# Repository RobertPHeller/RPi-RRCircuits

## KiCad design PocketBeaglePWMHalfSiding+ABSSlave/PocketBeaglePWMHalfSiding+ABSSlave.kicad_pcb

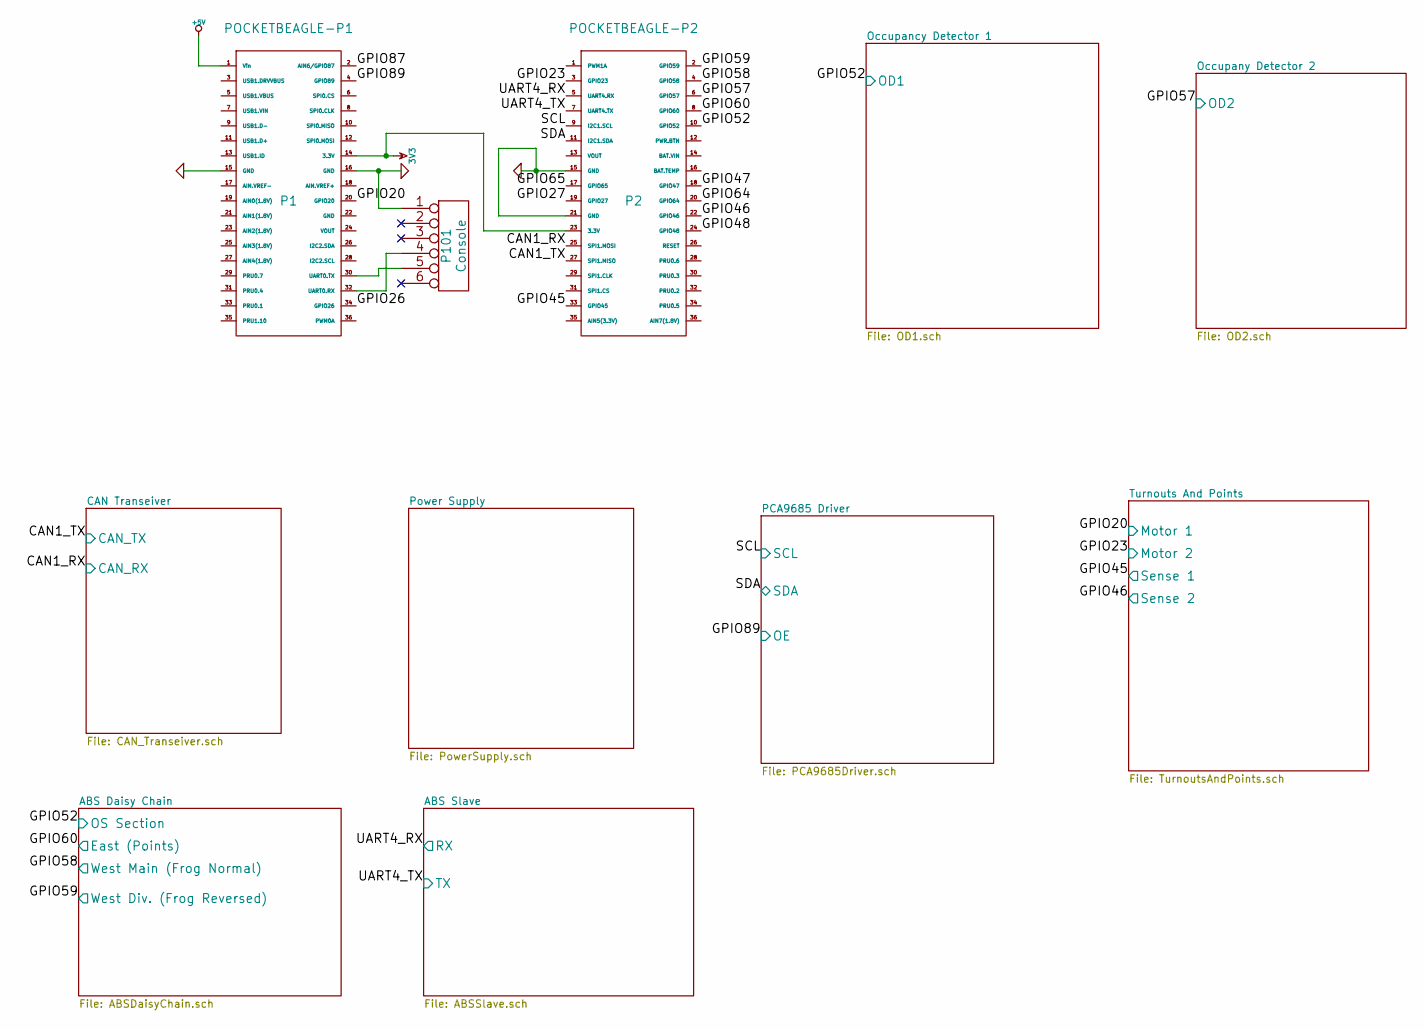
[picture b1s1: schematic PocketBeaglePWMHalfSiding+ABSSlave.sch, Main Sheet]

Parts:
P1: POCKETBEAGLE-P1
P2: POCKETBEAGLE-P2
P101: Console

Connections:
3V3: P1.14 (3.3V), P2.23 (3.3V); also elsewhere on the board
+5V: P1.1 (Vin); also elsewhere on the board
/ABS Daisy Chain/East (Points): P2.8 (GPIO60); also elsewhere on the board
/ABS Daisy Chain/West Div. (Frog Reversed): P2.2 (GPIO59); also elsewhere on the board
/ABS Daisy Chain/West Main (Frog Normal): P2.4 (GPIO58); also elsewhere on the board
/ABS Slave/RX: P2.5 (UART4.RX); also elsewhere on the board
/ABS Slave/TX: P2.7 (UART4.TX); also elsewhere on the board
/CAN Transeiver/CAN_RX: P2.25 (SPI1.MOSI); also elsewhere on the board
/CAN Transeiver/CAN_TX: P2.27 (SPI1.MISO); also elsewhere on the board
/Occupancy Detector 1/OD1: P2.10 (GPIO52); also elsewhere on the board
/Occupany Detector 2/OD2: P2.6 (GPIO57); also elsewhere on the board
/PCA9685 Driver/OE: P1.4 (GPIO89); also elsewhere on the board
/PCA9685 Driver/SCL: P2.9 (I2C1.SCL); also elsewhere on the board
/PCA9685 Driver/SDA: P2.11 (I2C1.SDA); also elsewhere on the board
/Turnouts And Points/Motor 1: P1.20 (GPIO20); also elsewhere on the board
/Turnouts And Points/Motor 2: P2.3 (GPIO23); also elsewhere on the board
/Turnouts And Points/Sense 1: P2.33 (GPIO45); also elsewhere on the board
/Turnouts And Points/Sense 2: P2.22 (GPIO46); also elsewhere on the board
GND: P1.15 (GND), P1.16 (GND), P2.15 (GND), P2.21 (GND), P101.1; also elsewhere on the board
unnamed: P1.32 (UART0.RX), P101.4
unnamed: P1.30 (UART0.TX), P101.5

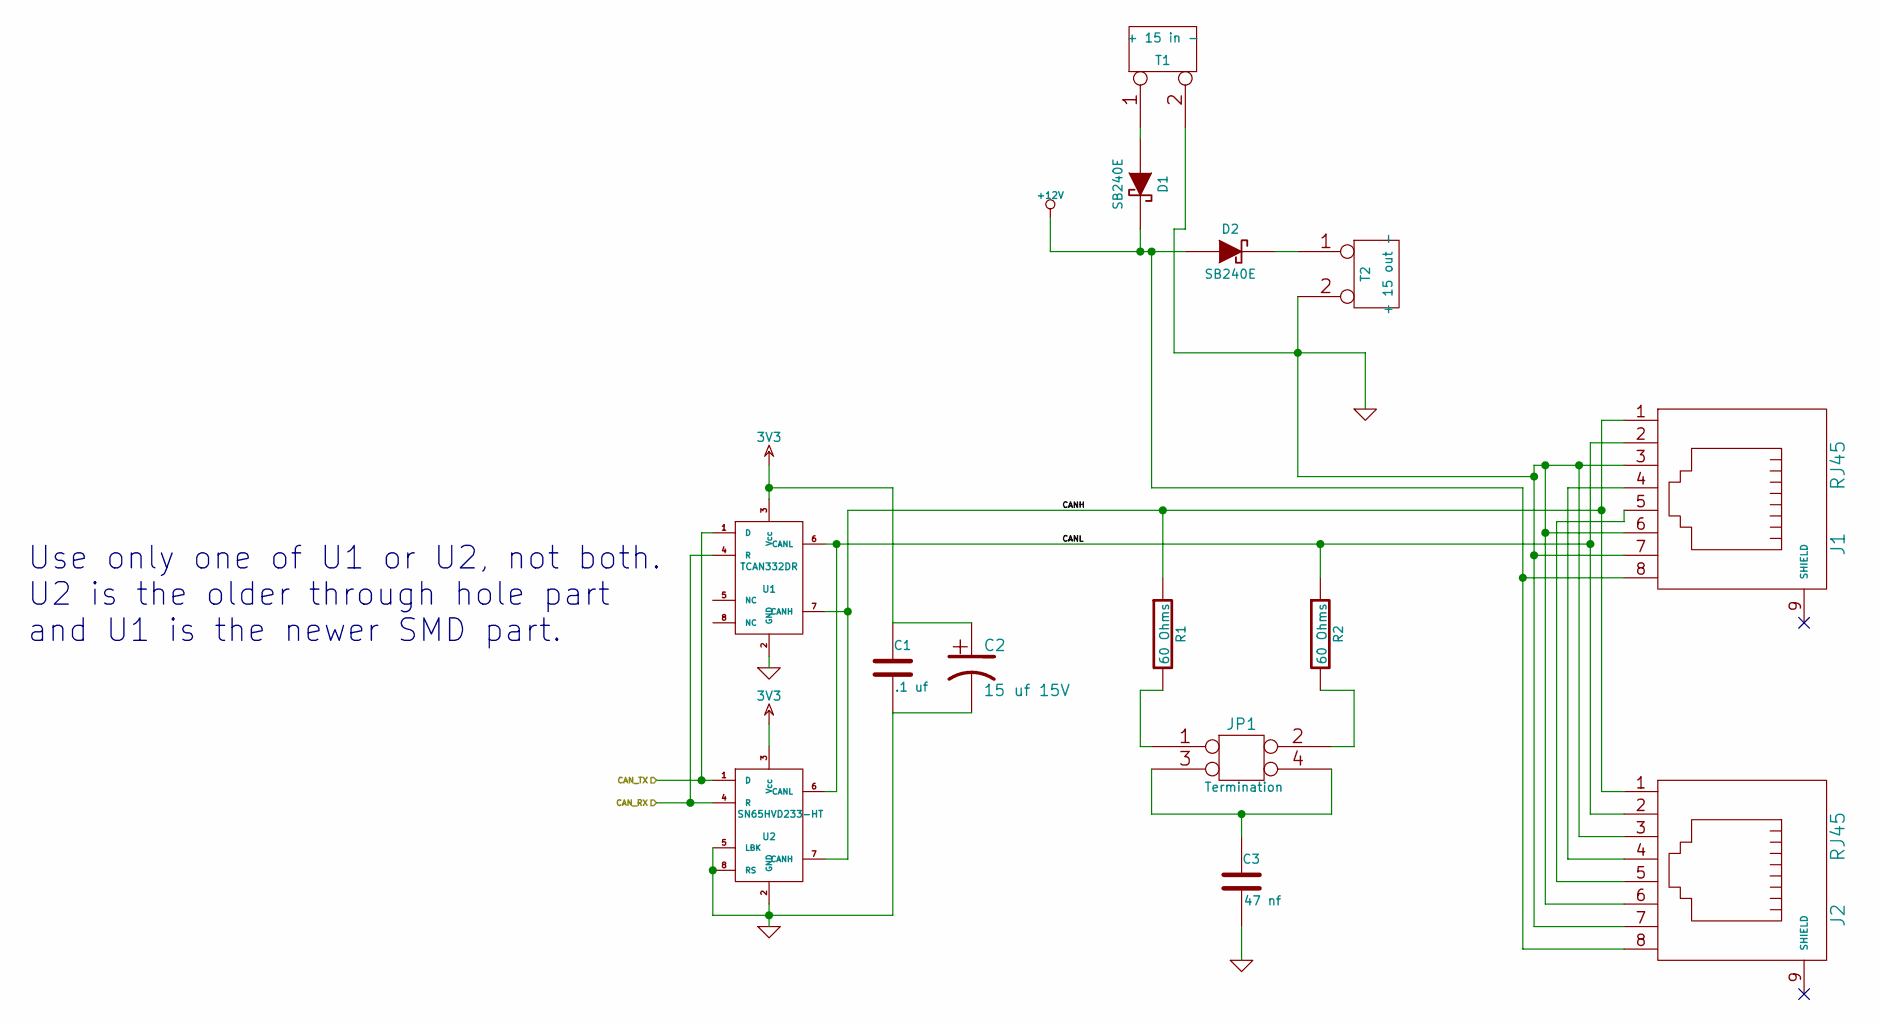
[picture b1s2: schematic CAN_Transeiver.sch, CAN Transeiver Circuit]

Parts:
C1: .1 uf
C2: 15 uf 15V
C3: 47 nf
D1, D2: SB240E
J1, J2: RJ45
JP1: Termination
R1, R2: 60 Ohms
T1: + 15 in -
T2: + 15 out -
U1: TCAN332DR
U2: SN65HVD233-HT

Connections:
3V3: C1.1, C2.1, U1.3 (Vcc), U2.3 (Vcc); also elsewhere on the board
+12V: D1.2 (K), D2.1 (A), J1.8, J2.8; also elsewhere on the board
/CAN Transeiver/CANH: J1.1, J2.1, R1.1, U1.7 (CANH), U2.7 (CANH)
/CAN Transeiver/CANL: J1.2, J2.2, R2.1, U1.6 (CANL), U2.6 (CANL)
/CAN Transeiver/CAN_RX: U1.4 (R), U2.4 (R); also elsewhere on the board
/CAN Transeiver/CAN_TX: U1.1 (D), U2.1 (D); also elsewhere on the board
GND: C1.2, C2.2, C3.2, J1.3, J1.6, J1.7, J2.3, J2.6, J2.7, T1.2 (PM), T2.2 (PM), U1.2 (GND), U2.2 (GND), U2.5 (LBK), U2.8 (RS); also elsewhere on the board
unnamed: J1.4, J2.4
unnamed: J1.5, J2.5
unnamed: D1.1 (A), T1.1
unnamed: D2.2 (K), T2.1
unnamed: JP1.1, R1.2
unnamed: JP1.2, R2.2
unnamed: C3.1, JP1.3, JP1.4

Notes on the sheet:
Use only one of U1 or U2, not both. U2 is the older through hole part and U1 is the newer SMD part.

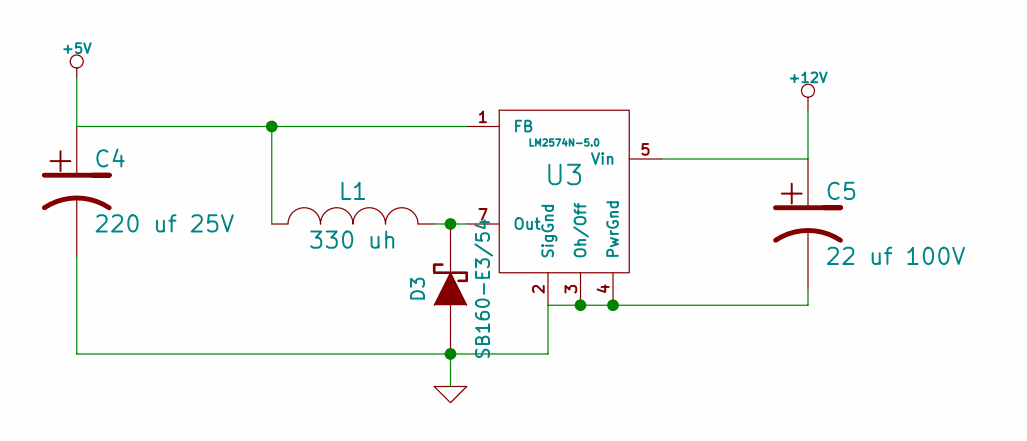
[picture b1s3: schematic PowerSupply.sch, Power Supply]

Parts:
C4: 220 uf 25V
C5: 22 uf 100V
D3: SB160-E3/54
L1: 330 uh
U3: LM2574N-5.0

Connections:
+5V: C4.1, L1.1, U3.1 (FB); also elsewhere on the board
+12V: C5.1, U3.5 (Vin); also elsewhere on the board
GND: C4.2, C5.2, D3.1 (A), U3.2 (SigGnd), U3.3 (Oh/Off), U3.4 (PwrGnd); also elsewhere on the board
unnamed: D3.2 (K), L1.2, U3.7 (Out)

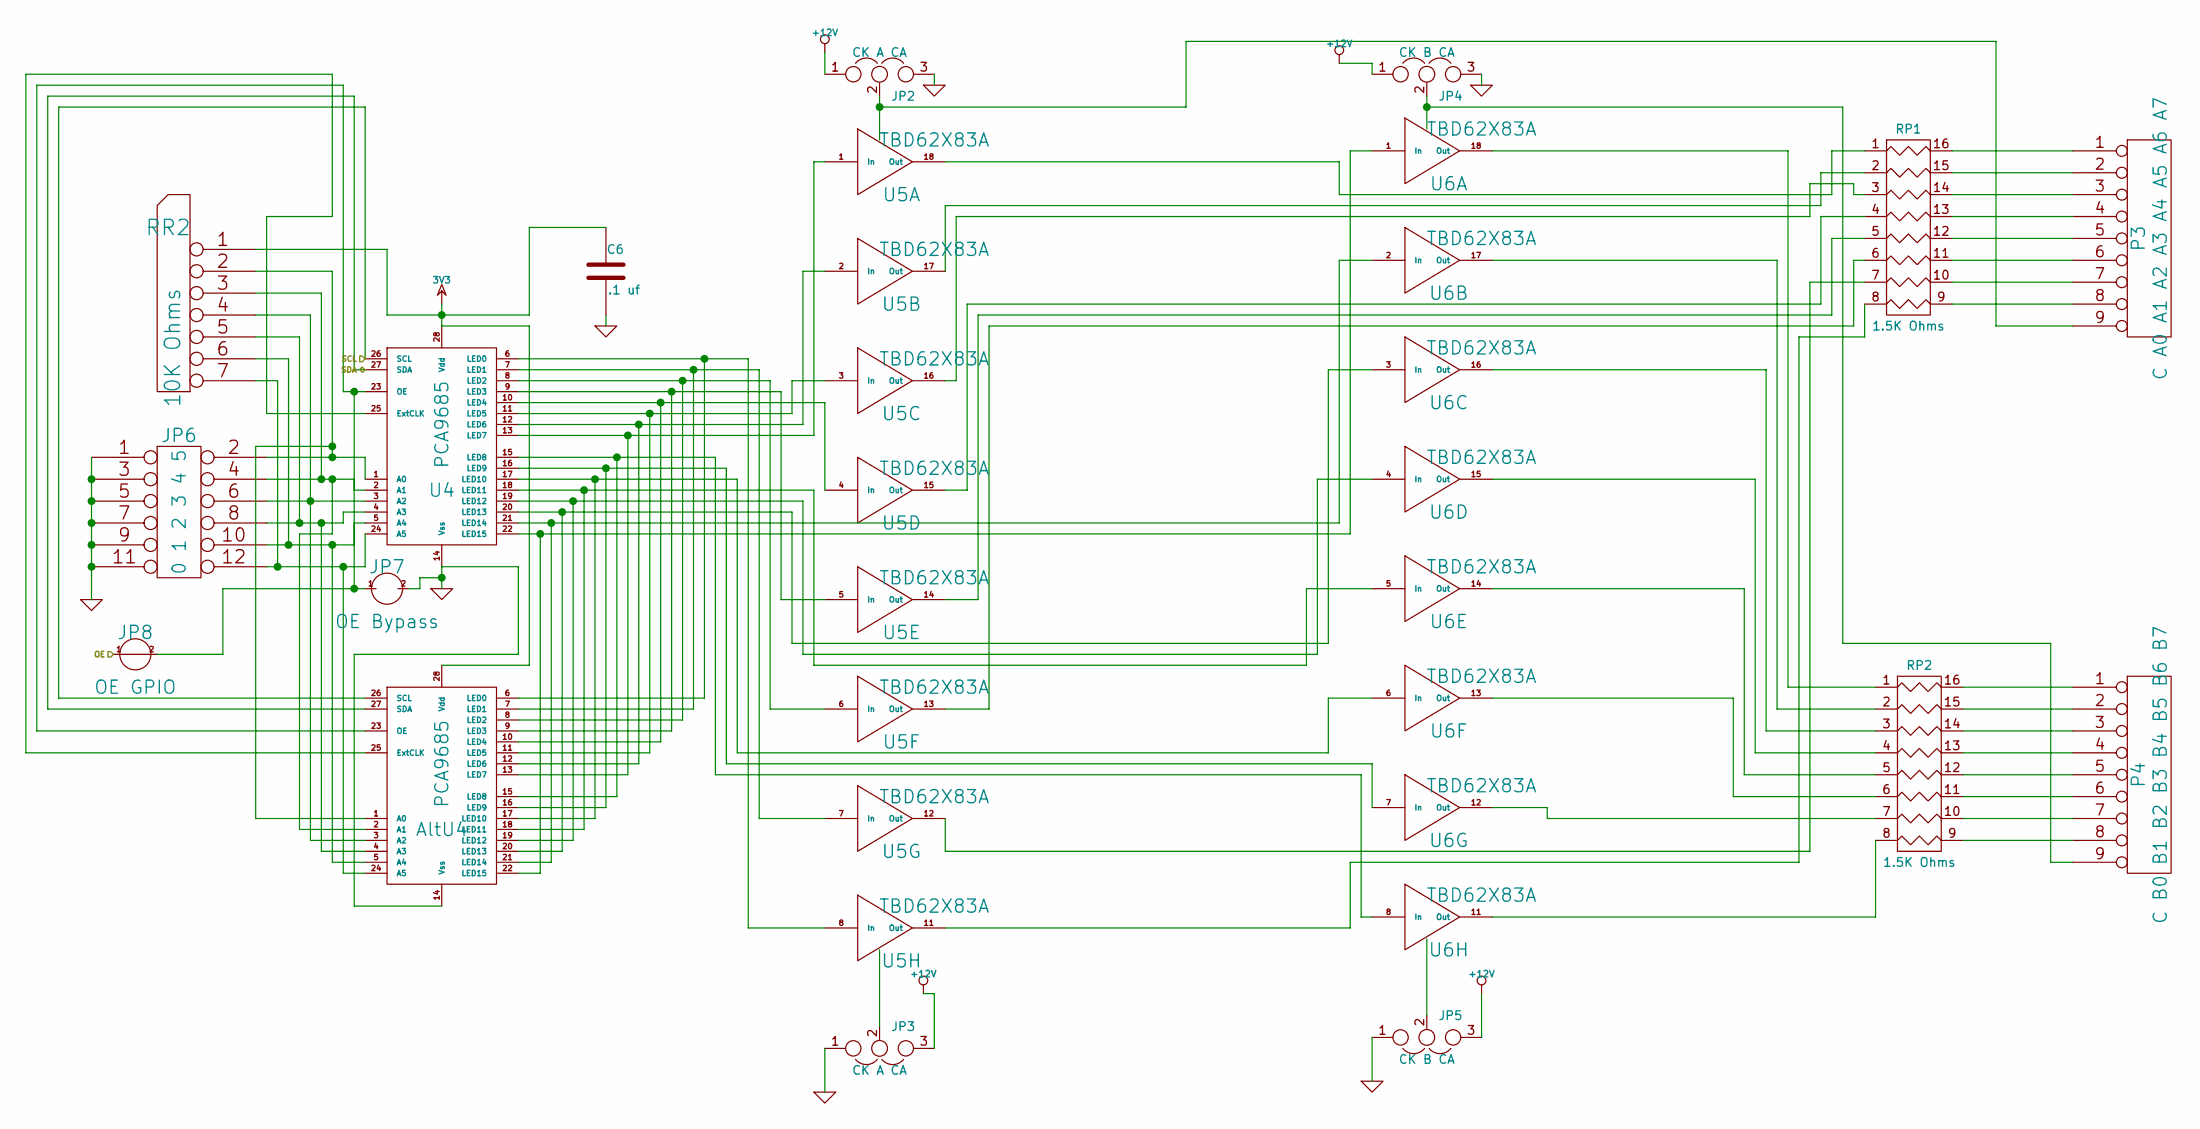
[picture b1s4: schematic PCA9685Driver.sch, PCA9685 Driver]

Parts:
AltU4: PCA9685
C6: .1 uf
JP2, JP3: CK A CA
JP4, JP5: CK B CA
JP6: 0 1 2 3 4 5
JP7: OE Bypass
JP8: OE GPIO
P3: C A0 A1 A2 A3 A4 A5 A6 A7
P4: C B0 B1 B2 B3 B4 B5 B6 B7
RP1, RP2: 1.5K Ohms
RR2: 10K Ohms
U4: PCA9685
U5, U6: TBD62X83A

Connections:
3V3: AltU4.28 (Vdd), C6.1, RR2.1 (COM), U4.28 (Vdd); also elsewhere on the board
+12V: JP2.1, JP3.3, JP4.1, JP5.3; also elsewhere on the board
/PCA9685 Driver/OE: JP8.1; also elsewhere on the board
/PCA9685 Driver/SCL: AltU4.26 (SCL), U4.26 (SCL); also elsewhere on the board
/PCA9685 Driver/SDA: AltU4.27 (SDA), U4.27 (SDA); also elsewhere on the board
GND: AltU4.14 (Vss), C6.2, JP2.3, JP3.1, JP4.3, JP5.1, JP6.1, JP6.3, JP6.5, JP6.7, JP6.9, JP6.11, JP7.2, U4.14 (Vss); also elsewhere on the board
unnamed: RP1.8, U5.11 (Out)
unnamed: RP2.1, U6.18 (Out)
unnamed: RP2.2, U6.17 (Out)
unnamed: RP2.3, U6.16 (Out)
unnamed: RP2.4, U6.15 (Out)
unnamed: RP1.5, U5.14 (Out)
unnamed: RP1.6, U5.13 (Out)
unnamed: RP1.7, U5.12 (Out)
unnamed: AltU4.18 (LED11), U4.18 (LED11), U6.5 (In)
unnamed: RP2.8, U6.11 (Out)
unnamed: RP2.5, U6.14 (Out)
unnamed: RP2.6, U6.13 (Out)
unnamed: RP2.7, U6.12 (Out)
unnamed: JP5.2, U6.9 (IC)
unnamed: JP3.2, U5.9 (IC)
unnamed: JP2.2, P3.9, U5.10 (OC)
unnamed: JP4.2, P4.9, U6.10 (OC)
unnamed: RP1.3, U5.16 (Out)
unnamed: RP1.1, U5.18 (Out)
unnamed: RP1.2, U5.17 (Out)
unnamed: RP1.4, U5.15 (Out)
unnamed: P4.2, RP2.15 (R2)
unnamed: P3.1, RP1.16 (R1)
unnamed: P3.2, RP1.15 (R2)
unnamed: P3.3, RP1.14 (R3)
unnamed: P3.4, RP1.13 (R4)
unnamed: P3.6, RP1.11 (R6)
unnamed: P3.7, RP1.10 (R7)
unnamed: P3.8, RP1.9 (R8)
unnamed: P4.1, RP2.16 (R1)
unnamed: P4.3, RP2.14 (R3)
unnamed: P4.4, RP2.13 (R4)
unnamed: P4.5, RP2.12 (R5)
unnamed: P4.6, RP2.11 (R6)
unnamed: P4.7, RP2.10 (R7)
unnamed: P4.8, RP2.9 (R8)
unnamed: AltU4.23 (OE), JP7.1, JP8.2, U4.23 (OE)
unnamed: P3.5, RP1.12 (R5)
unnamed: AltU4.25 (ExtCLK), U4.25 (ExtCLK)
unnamed: AltU4.1 (A0), JP6.2, RR2.2, U4.1 (A0)
unnamed: AltU4.2 (A1), JP6.4, RR2.3, U4.2 (A1)
unnamed: AltU4.7 (LED1), U4.7 (LED1), U5.7 (In)
unnamed: AltU4.4 (A3), JP6.8, RR2.5, U4.4 (A3)
unnamed: AltU4.24 (A5), JP6.12, RR2.7, U4.24 (A5)
unnamed: AltU4.5 (A4), JP6.10, RR2.6, U4.5 (A4)
unnamed: AltU4.3 (A2), JP6.6, RR2.4, U4.3 (A2)
unnamed: AltU4.15 (LED8), U4.15 (LED8), U6.8 (In)
unnamed: AltU4.16 (LED9), U4.16 (LED9), U6.7 (In)
unnamed: AltU4.17 (LED10), U4.17 (LED10), U6.6 (In)
unnamed: AltU4.19 (LED12), U4.19 (LED12), U6.4 (In)
unnamed: AltU4.21 (LED14), U4.21 (LED14), U6.2 (In)
unnamed: AltU4.13 (LED7), U4.13 (LED7), U5.1 (In)
unnamed: AltU4.6 (LED0), U4.6 (LED0), U5.8 (In)
unnamed: AltU4.20 (LED13), U4.20 (LED13), U6.3 (In)
unnamed: AltU4.11 (LED5), U4.11 (LED5), U5.3 (In)
unnamed: AltU4.10 (LED4), U4.10 (LED4), U5.4 (In)
unnamed: AltU4.8 (LED2), U4.8 (LED2), U5.6 (In)
unnamed: AltU4.12 (LED6), U4.12 (LED6), U5.2 (In)
unnamed: AltU4.22 (LED15), U4.22 (LED15), U6.1 (In)
unnamed: AltU4.9 (LED3), U4.9 (LED3), U5.5 (In)

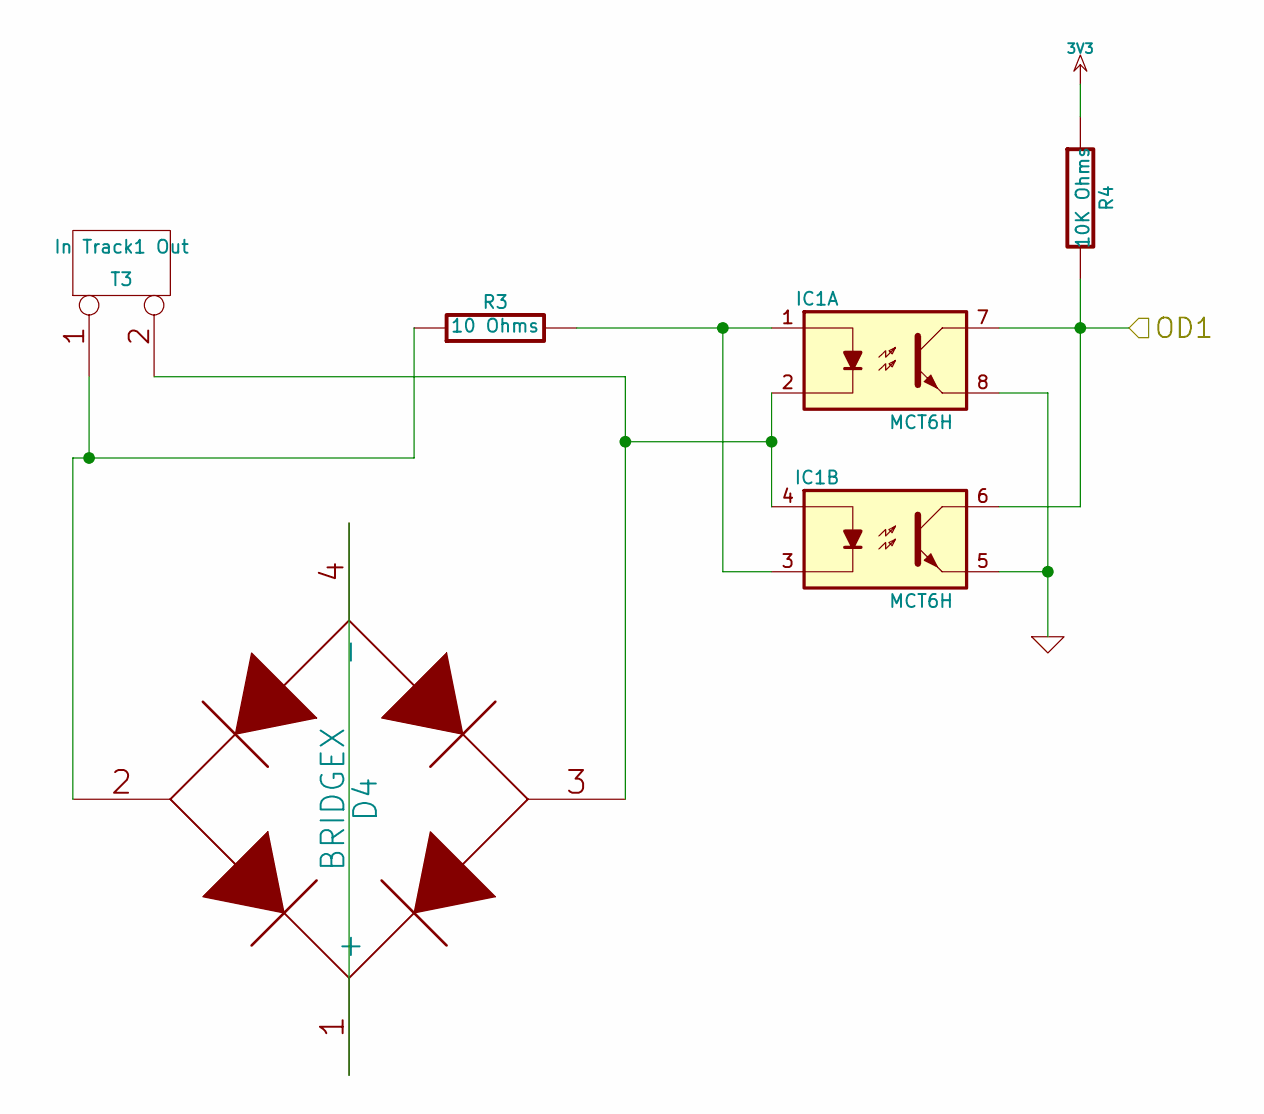
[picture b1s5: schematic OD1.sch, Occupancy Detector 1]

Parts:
D4: BRIDGEX
IC1: MCT6H; DIP-8__300
R3: 10 Ohms
R4: 10K Ohms
T3: In Track1 Out

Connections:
3V3: R4.1; also elsewhere on the board
/Occupancy Detector 1/OD1: IC1.6, IC1.7, R4.2; also elsewhere on the board
GND: IC1.5, IC1.8; also elsewhere on the board
unnamed: IC1.1, IC1.3, R3.2
unnamed: D4.3, IC1.2, IC1.4, T3.2 (PM)
unnamed: D4.2, R3.1, T3.1
unnamed: D4.1 (+), D4.4 (-)

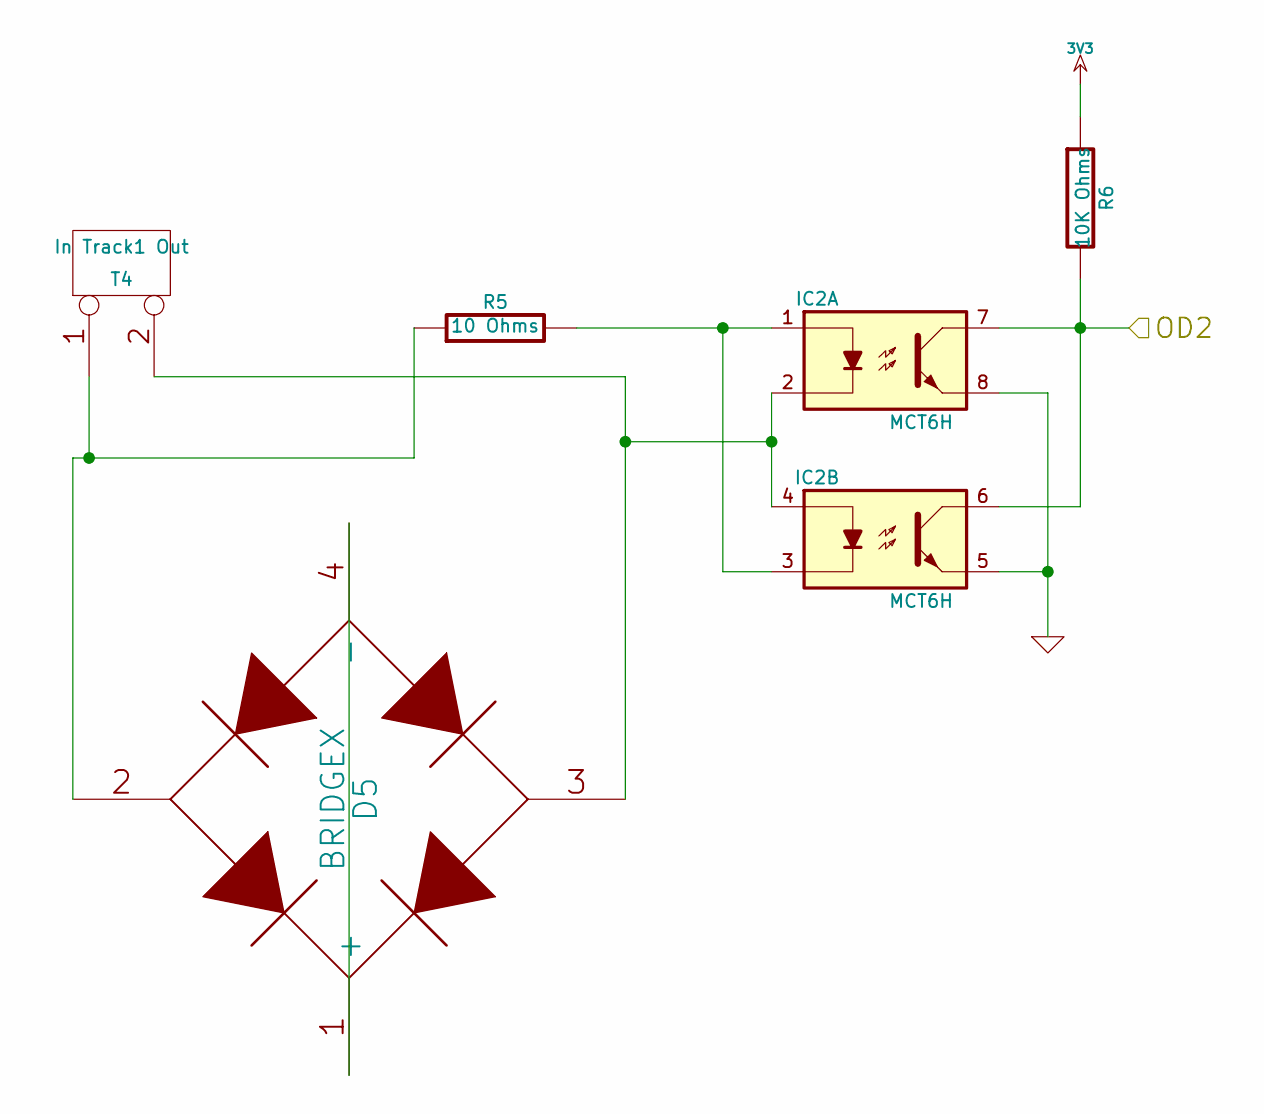
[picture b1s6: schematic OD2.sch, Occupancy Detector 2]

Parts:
D5: BRIDGEX
IC2: MCT6H; DIP-8__300
R5: 10 Ohms
R6: 10K Ohms
T4: In Track1 Out

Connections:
3V3: R6.1; also elsewhere on the board
/Occupany Detector 2/OD2: IC2.6, IC2.7, R6.2; also elsewhere on the board
GND: IC2.5, IC2.8; also elsewhere on the board
unnamed: IC2.1, IC2.3, R5.2
unnamed: D5.3, IC2.2, IC2.4, T4.2 (PM)
unnamed: D5.2, R5.1, T4.1
unnamed: D5.1 (+), D5.4 (-)

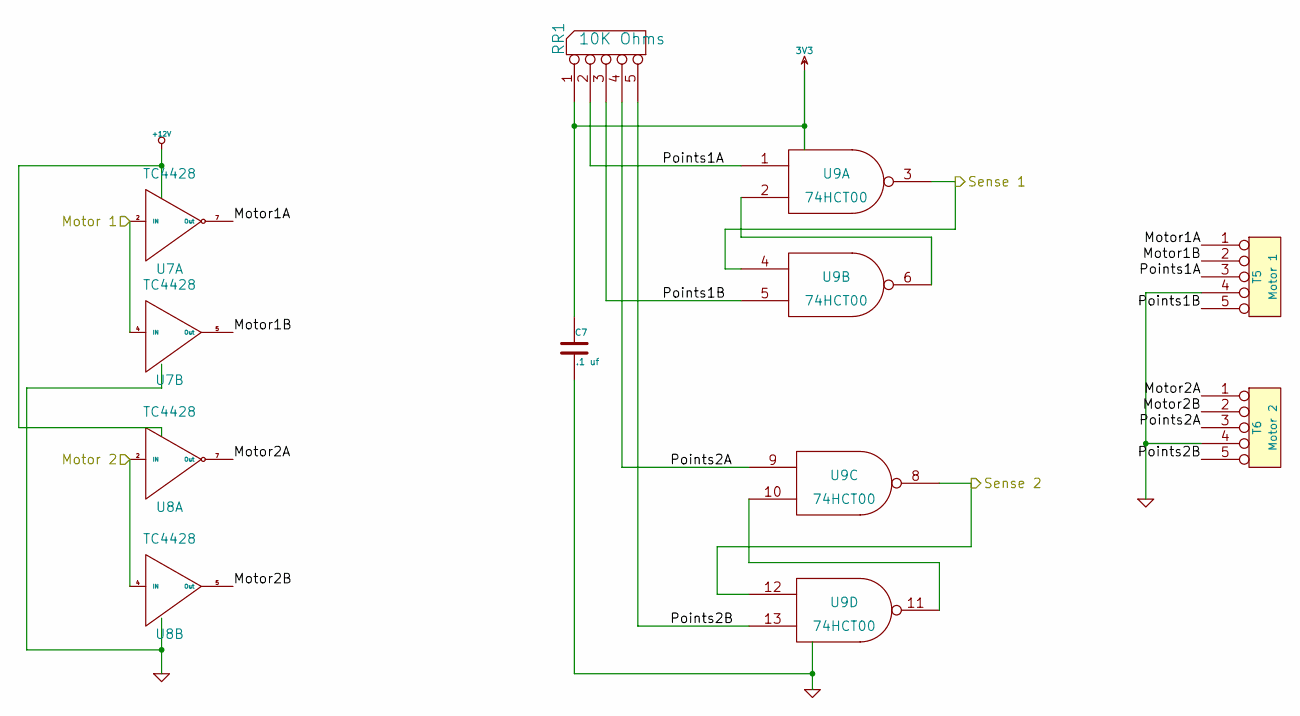
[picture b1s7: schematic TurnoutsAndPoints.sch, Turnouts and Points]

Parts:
C7: .1 uf
RR1: 10K Ohms
T5: Motor 1
T6: Motor 2
U7, U8: TC4428
U9: 74HCT00

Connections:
3V3: C7.1, RR1.1 (COM), U9.14 (VCC); also elsewhere on the board
+12V: U7.6 (Vdd), U8.6 (Vdd); also elsewhere on the board
/Turnouts And Points/Motor1A: T5.1, U7.7 (Out)
/Turnouts And Points/Motor1B: T5.2, U7.5 (Out)
/Turnouts And Points/Motor2A: T6.1, U8.7 (Out)
/Turnouts And Points/Motor2B: T6.2, U8.5 (Out)
/Turnouts And Points/Motor 1: U7.2 (IN), U7.4 (IN); also elsewhere on the board
/Turnouts And Points/Motor 2: U8.2 (IN), U8.4 (IN); also elsewhere on the board
/Turnouts And Points/Points1A: RR1.2, T5.3, U9.1
/Turnouts And Points/Points1B: RR1.3, T5.5, U9.5
/Turnouts And Points/Points2A: RR1.4, T6.3, U9.9
/Turnouts And Points/Points2B: RR1.5, T6.5, U9.13
/Turnouts And Points/Sense 1: U9.3, U9.4; also elsewhere on the board
/Turnouts And Points/Sense 2: U9.8, U9.12; also elsewhere on the board
GND: C7.2, T5.4, T6.4, U7.3 (GND), U8.3 (GND), U9.7 (GND); also elsewhere on the board
unnamed: U9.2, U9.6
unnamed: U9.10, U9.11

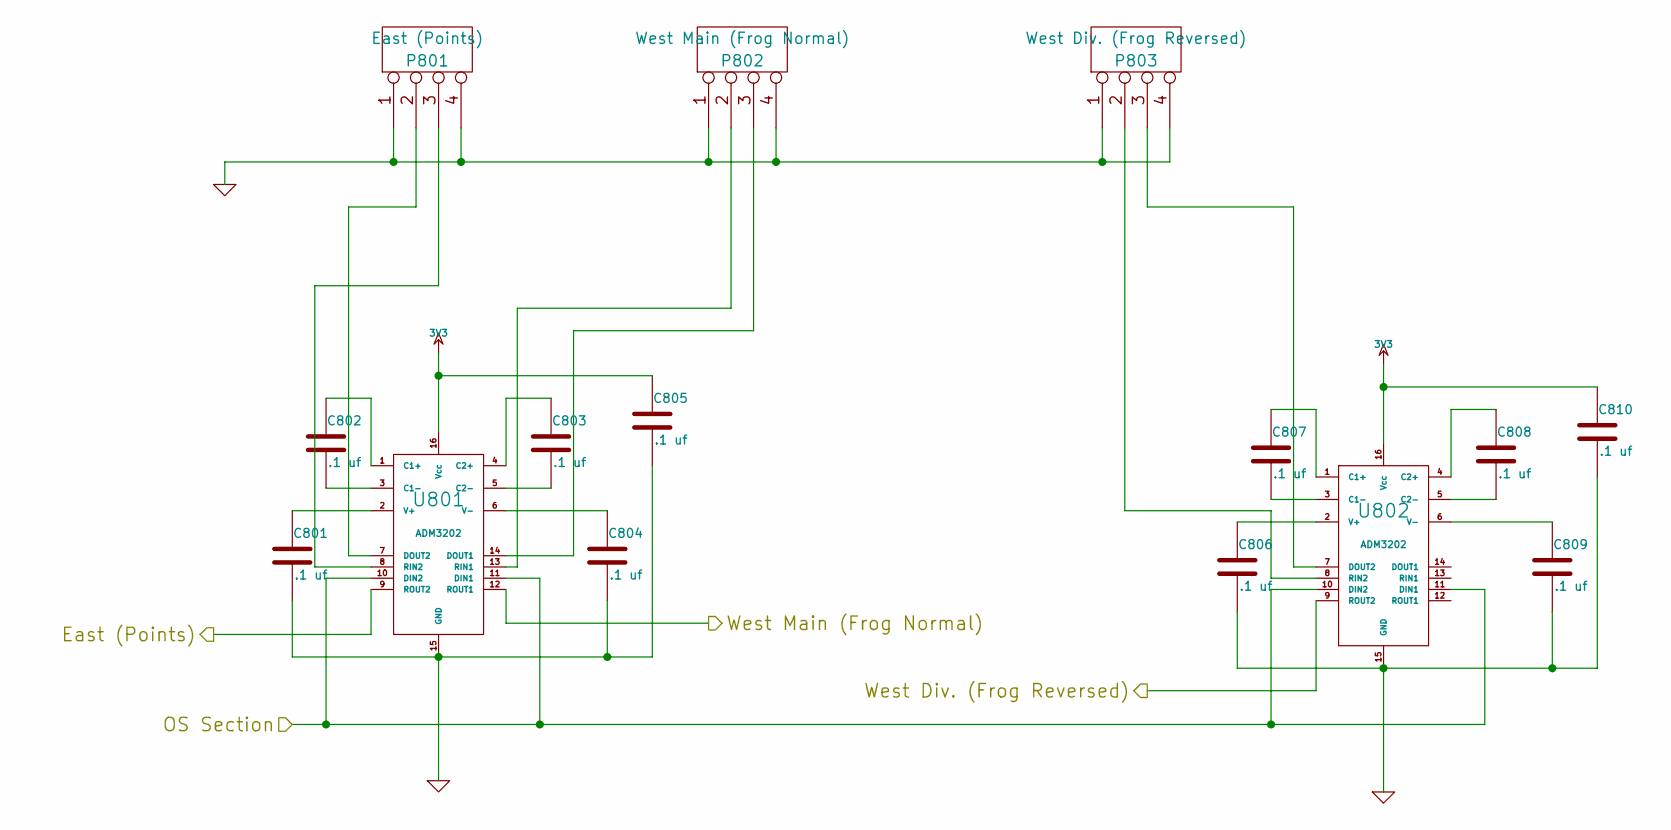
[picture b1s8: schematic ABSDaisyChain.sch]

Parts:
C801, C802, C803, C804, C805, C806, C807, C808, C809, C810: .1 uf
P801: East (Points)
P802: West Main (Frog Normal)
P803: West Div. (Frog Reversed)
U801, U802: ADM3202

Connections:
3V3: C805.1, C810.1, U801.16 (Vcc), U802.16 (Vcc); also elsewhere on the board
/ABS Daisy Chain/East (Points): U801.9 (ROUT2); also elsewhere on the board
/ABS Daisy Chain/West Div. (Frog Reversed): U802.9 (ROUT2); also elsewhere on the board
/ABS Daisy Chain/West Main (Frog Normal): U801.12 (ROUT1); also elsewhere on the board
/Occupancy Detector 1/OD1: U801.10 (DIN2), U801.11 (DIN1), U802.10 (DIN2), U802.11 (DIN1); also elsewhere on the board
GND: C801.2, C804.2, C805.2, C806.2, C809.2, C810.2, P801.1, P801.4, P802.1, P802.4, P803.1, P803.4, U801.15 (GND), U802.15 (GND); also elsewhere on the board
unnamed: C808.1, U802.4 (C2+)
unnamed: C807.2, U802.3 (C1-)
unnamed: C807.1, U802.1 (C1+)
unnamed: C808.2, U802.5 (C2-)
unnamed: C806.1, U802.2 (V+)
unnamed: C809.1, U802.6 (V-)
unnamed: P801.3, U801.8 (RIN2)
unnamed: P802.2, U801.13 (RIN1)
unnamed: P803.2, U802.8 (RIN2)
unnamed: P801.2, U801.7 (DOUT2)
unnamed: P802.3, U801.14 (DOUT1)
unnamed: P803.3, U802.7 (DOUT2)
unnamed: C802.1, U801.1 (C1+)
unnamed: C803.1, U801.4 (C2+)
unnamed: C803.2, U801.5 (C2-)
unnamed: C804.1, U801.6 (V-)
unnamed: C802.2, U801.3 (C1-)
unnamed: C801.1, U801.2 (V+)

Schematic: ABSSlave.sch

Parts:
P901: ABS Slave Bus
R901, R902: 60 Ohms
U901: MAX3490AE

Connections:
3V3: U901.1 (Vcc); also elsewhere on the board
/ABS Slave/RX: U901.2 (R); also elsewhere on the board
/ABS Slave/TX: U901.3 (D); also elsewhere on the board
GND: P901.5, U901.4 (GND); also elsewhere on the board
unnamed: P901.1, R902.1, U901.5 (Y)
unnamed: P901.2, R902.2, U901.6 (Z)
unnamed: P901.3, R901.2, U901.7 (B)
unnamed: P901.4, R901.1, U901.8 (A)

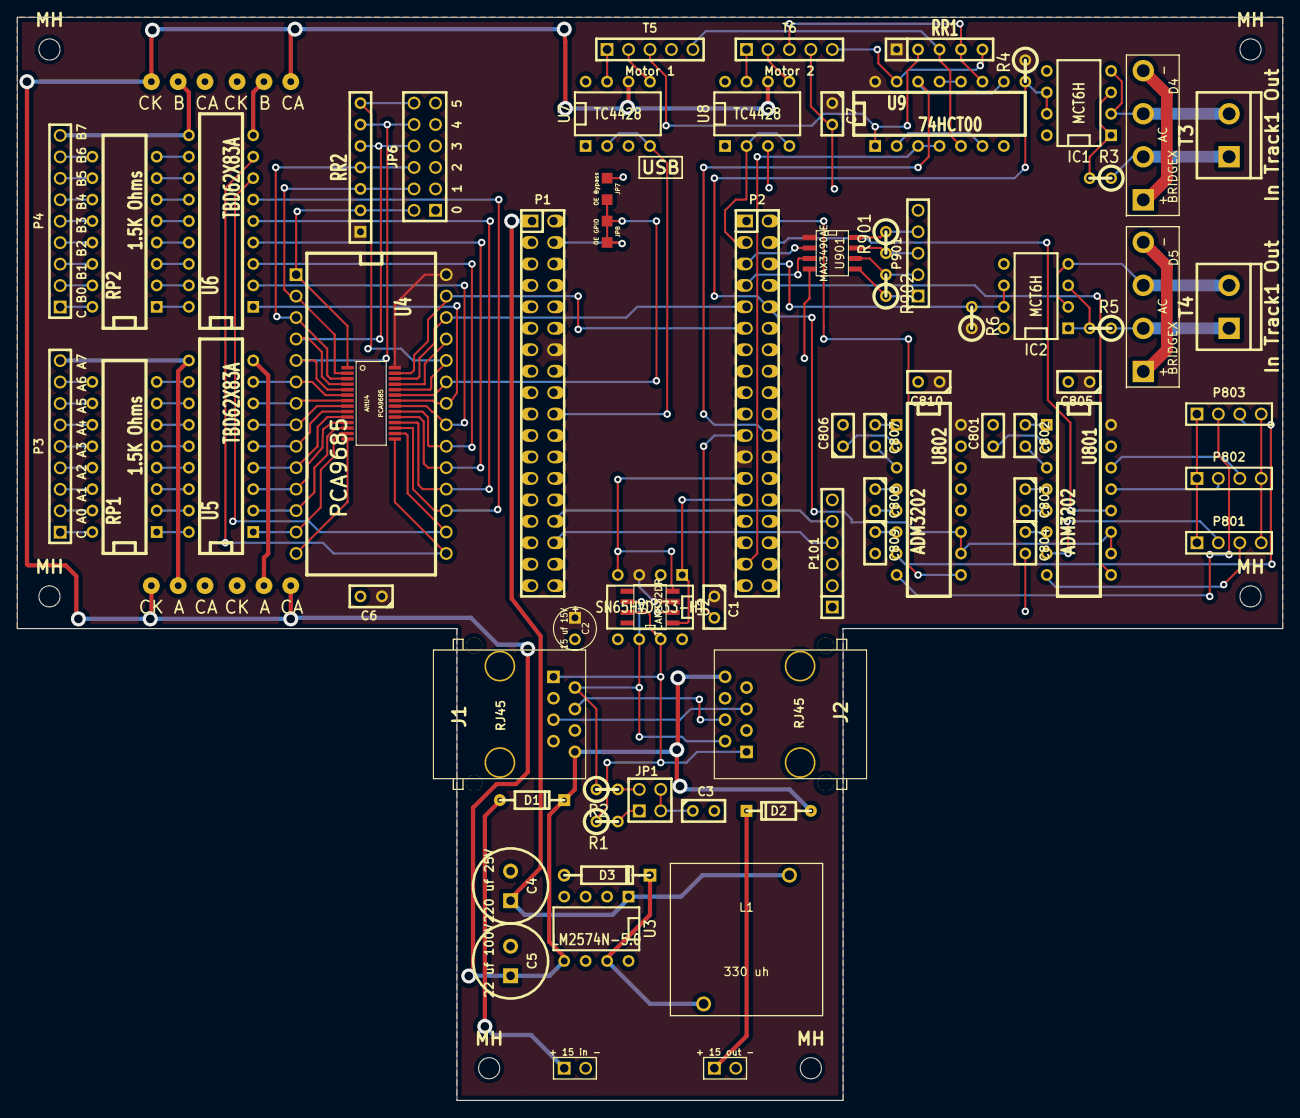
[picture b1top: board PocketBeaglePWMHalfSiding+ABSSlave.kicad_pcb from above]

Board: 2 copper layers, 149.9 x 128.3 mm, 81 parts (0 on the bottom side), 132 nets.

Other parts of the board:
MH: MountingHole_2-5mm_RevA_Date21Jun2010
MH#2, MH#3, MH#4, MH#5, MH#6: MountingHole_2-5mm_RevA_Date21Jun2010

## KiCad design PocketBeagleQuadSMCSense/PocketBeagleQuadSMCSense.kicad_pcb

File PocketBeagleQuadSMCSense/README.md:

# PocketBeagleQuadSMCSense

PocketBeagle Quad Stall Motor w/ Sense.

* [Order this board from The Country Robot](https://www.thecountryrobot.com/product/quad-stall-motor-control-and-sense-for-pocket-beagle-bare-circuit-board-w-doc/)
* [Order this board from PCBWay](https://www.pcbway.com/project/shareproject/Pocket_Beagle_Quad_StallMotor_w_Sense_base_board__includes_LCC_CAN_and_power_supply.html)

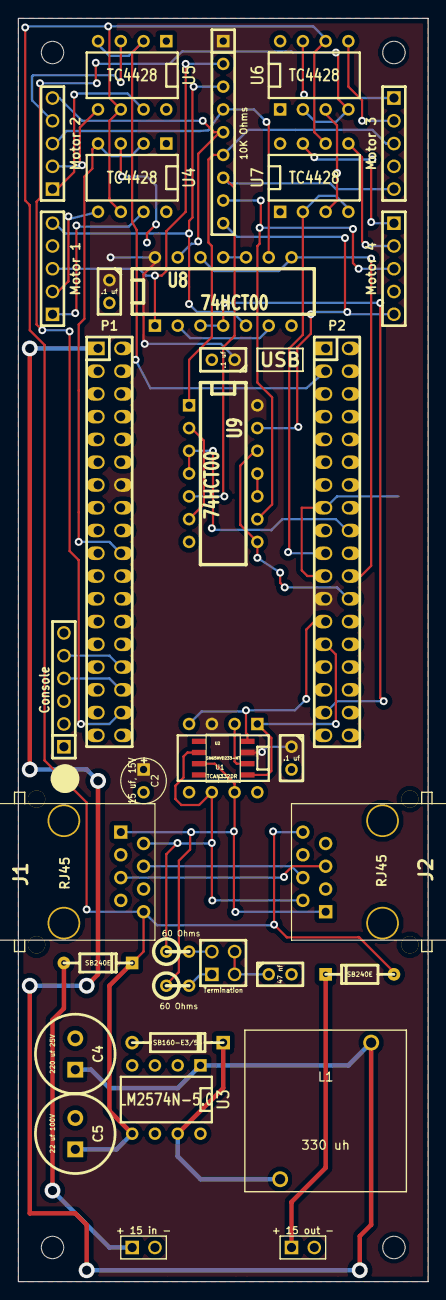
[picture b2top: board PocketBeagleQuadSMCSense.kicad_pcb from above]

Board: 2 copper layers, 45.7 x 141.0 mm, 39 parts (0 on the bottom side), 46 nets.

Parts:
C1, C6, C7: .1 uf; C1
C2: 15 uf, 15V; C1V5
C3: 47 nf; C1
C4: 220 uf 25V; C1-3V8
C5: 22 uf 100V; C1-3V8
D1, D2: SB240E; DO-35
D3: SB160-E3/54; DO-41
J1, J2: RJ45; RJ45_8N-S
JMP1: Termination; PIN_ARRAY_2X2
L1: 330 uh; PE-LowProfile
MH: MountingHole_2-5mm_RevA_Date21Jun2010
MH#2, MH#3, MH#4: MountingHole_2-5mm_RevA_Date21Jun2010
P1: POCKETBEAGLE-P1; pin_socket_18x2
P2: POCKETBEAGLE-P2; pin_socket_18x2
P101: Console; PIN_ARRAY-6X1
R1, R2: 60 Ohms; R1
RR1: 10K Ohms; SIL-9
T1: + 15 in -; ScrewTerm2.54-2
T2: + 15 out -; ScrewTerm2.54-2
T3: Motor 1; ScrewTerm_2.54-5
T4: Motor 2; ScrewTerm_2.54-5
T5: Motor 3; ScrewTerm_2.54-5
T6: Motor 4; ScrewTerm_2.54-5
U1: TCAN332DR; SOIC-8_N
U2: SN65HVD233-HT; DIP-8__300
U3: LM2574N-5.0; DIP-8__300
U4, U5, U6, U7: TC4428; DIP-8__300
U8, U9: 74HCT00; DIP-14__300

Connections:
+3.3V: C1.1, C2.1, C6.1, C7.1, P1.14, P2.23, RR1.1, U1.3, U2.3, U8.14, U9.14
+12V: C5.1, D1.2, D2.1, J1.8, J2.8, U3.5, U4.6, U5.6, U6.6, U7.6
/CAN1_RX: P2.25, U1.4, U2.4
/CAN1_TX: P2.27, U1.1, U2.1
/CANH: J1.1, J2.1, R1.1, U1.7, U2.7
/CANL: J1.2, J2.2, R2.1, U1.6, U2.6
/Power Supply/5V Out: C4.1, L1.1, P1.1, U3.1
/Quad SMC Sense/Motor1A: T3.1, U4.7
/Quad SMC Sense/Motor1B: T3.2, U4.5
/Quad SMC Sense/Motor2A: T4.1, U5.7
/Quad SMC Sense/Motor2B: T4.2, U5.5
/Quad SMC Sense/Motor3A: T5.1, U6.7
/Quad SMC Sense/Motor3B: T5.2, U6.5
/Quad SMC Sense/Motor4A: T6.1, U7.7
/Quad SMC Sense/Motor4B: T6.2, U7.5
/Quad SMC Sense/Motor 1: P1.20, U4.2, U4.4
/Quad SMC Sense/Motor 2: P2.3, U5.2, U5.4
/Quad SMC Sense/Motor 3: P1.34, U6.2, U6.4
/Quad SMC Sense/Motor 4: P2.19, U7.2, U7.4
/Quad SMC Sense/Sense1A: RR1.2, T3.3, U8.1
/Quad SMC Sense/Sense1B: RR1.3, T3.5, U8.5
/Quad SMC Sense/Sense2A: RR1.4, T4.3, U8.9
/Quad SMC Sense/Sense2B: RR1.5, T4.5, U8.13
/Quad SMC Sense/Sense3A: RR1.6, T5.3, U9.1
/Quad SMC Sense/Sense3B: RR1.7, T5.5, U9.5
/Quad SMC Sense/Sense4A: RR1.8, T6.3, U9.9
/Quad SMC Sense/Sense4B: RR1.9, T6.5, U9.13
/Quad SMC Sense/Sense 1: P2.33, U8.3, U8.4
/Quad SMC Sense/Sense 2: P2.22, U8.8, U8.12
/Quad SMC Sense/Sense 3: P2.18, U9.3, U9.4
/Quad SMC Sense/Sense 4: P2.24, U9.8, U9.12
GND: C1.2, C2.2, C3.2, C4.2, C5.2, C6.2, C7.2, D3.1, J1.3, J1.6, J1.7, J2.3, J2.6, J2.7, P1.15, P1.16, P1.22, P2.15, P2.21, P101.1, T1.2, T2.2, T3.4, T4.4, T5.4, T6.4, U1.2, U2.2, U2.5, U2.8, U3.2, U3.3, U3.4, U4.3, U5.3, U6.3, U7.3, U8.7, U9.7
unnamed: P1.32, P101.4
unnamed: J1.5, J2.5
unnamed: J1.4, J2.4
unnamed: JMP1.1, R1.2
unnamed: JMP1.2, R2.2
unnamed: C3.1, JMP1.3, JMP1.4
unnamed: P1.30, P101.5
unnamed: D2.2, T2.1
unnamed: D1.1, T1.1
unnamed: D3.2, L1.2, U3.7
unnamed: U9.10, U9.11
unnamed: U9.2, U9.6
unnamed: U8.2, U8.6
unnamed: U8.10, U8.11

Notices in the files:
QuadSMC/QuadSMC.kicad_pcb:
Copyright 2016 Deeowoods Software
